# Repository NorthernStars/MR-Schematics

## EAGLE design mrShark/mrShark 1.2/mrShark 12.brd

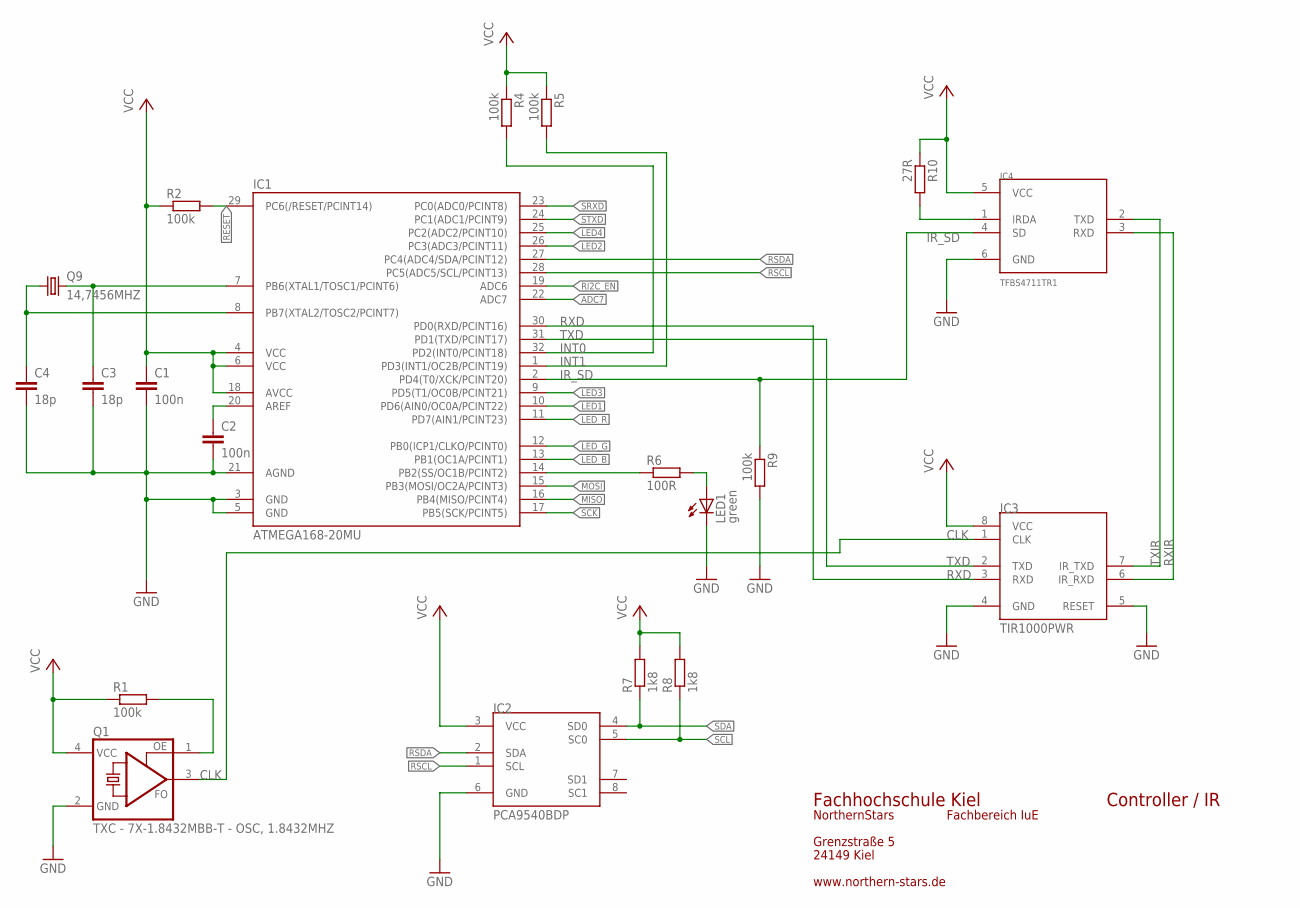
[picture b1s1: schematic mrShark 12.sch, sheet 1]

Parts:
C1, C2: 100n; C0201
C3, C4: 18p; C0201
IC1: ATMEGA168-20MU; MLF32
IC2: PCA9540BDP; TSSOP8
IC3: TIR1000PWR; PW_R-PDSO-G08
IC4: TFBS4711TR1; TFBS4711
LED1: green; CHIPLED_0603
Q1: TXC - 7X-1.8432MBB-T - OSC, 1.8432MHZ; 3.2X2.5
Q9: 14,7456MHZ; TXC_7B_SERIES
R1, R2, R4, R5, R9: 100k; R0201
R6: 100R; R0201
R7, R8: 1k8; R0201
R10: 27R; R0201

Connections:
ADC7: IC1.22 (ADC7); also elsewhere on the board
CLK: IC3.1 (CLK), Q1.3 (FO)
GND: C1.2, C2.2, C3.2, C4.2, IC1.3 (GND), IC1.5 (GND), IC1.21 (AGND), IC2.6 (GND), IC3.4 (GND), IC3.5 (RESET), IC4.6 (GND), LED1.C, Q1.2 (GND), R9.2; also elsewhere on the board
INT0: IC1.32 (PD2(INT0/PCINT18)), R4.2; also elsewhere on the board
INT1: IC1.1 (PD3(INT1/OC2B/PCINT19)), R5.2; also elsewhere on the board
IRDA: IC4.1 (IRDA), R10.2
IR_SD: IC1.2 (PD4(T0/XCK/PCINT20)), IC4.4 (SD), R9.1
LED1: IC1.10 (PD6(AIN0/OC0A/PCINT22)); also elsewhere on the board
LED2: IC1.26 (PC3(ADC3/PCINT11)); also elsewhere on the board
LED3: IC1.9 (PD5(T1/OC0B/PCINT21)); also elsewhere on the board
LED4: IC1.25 (PC2(ADC2/PCINT10)); also elsewhere on the board
LED_B: IC1.13 (PB1(OC1A/PCINT1)); also elsewhere on the board
LED_G: IC1.12 (PB0(ICP1/CLKO/PCINT0)); also elsewhere on the board
LED_R: IC1.11 (PD7(AIN1/PCINT23)); also elsewhere on the board
MISO: IC1.16 (PB4(MISO/PCINT4)); also elsewhere on the board
MOSI: IC1.15 (PB3(MOSI/OC2A/PCINT3)); also elsewhere on the board
unnamed: IC1.14 (PB2(SS/OC1B/PCINT2)), R6.1
unnamed: Q1.1 (OE), R1.2
unnamed: LED1.A, R6.2
unnamed: C2.1, IC1.20 (AREF)
RESET: IC1.29 (PC6(/RESET/PCINT14)), R2.2; also elsewhere on the board
RI2C_EN: IC1.19 (ADC6)
RSCL: IC1.28 (PC5(ADC5/SCL/PCINT13)), IC2.1 (SCL); also elsewhere on the board
RSDA: IC1.27 (PC4(ADC4/SDA/PCINT12)), IC2.2 (SDA); also elsewhere on the board
RXD: IC1.30 (PD0(RXD/PCINT16)), IC3.3 (RXD)
RXIR: IC3.6 (IR_RXD), IC4.3 (RXD)
SCK: IC1.17 (PB5(SCK/PCINT5)); also elsewhere on the board
SCL: IC2.5 (SC0), R8.1; also elsewhere on the board
SDA: IC2.4 (SD0), R7.1; also elsewhere on the board
SRXD: IC1.23 (PC0(ADC0/PCINT8)); also elsewhere on the board
STXD: IC1.24 (PC1(ADC1/PCINT9)); also elsewhere on the board
TXD: IC1.31 (PD1(TXD/PCINT17)), IC3.2 (TXD)
TXIR: IC3.7 (IR_TXD), IC4.2 (TXD)
VCC: C1.1, IC1.4 (VCC), IC1.6 (VCC), IC1.18 (AVCC), IC2.3 (VCC), IC3.8 (VCC), IC4.5 (VCC), Q1.4 (VCC), R1.1, R2.1, R4.1, R5.1, R7.2, R8.2, R10.1; also elsewhere on the board
XTAL1: C3.1, IC1.7 (PB6(XTAL1/TOSC1/PCINT6)), Q9.3 (2)
XTAL2: C4.1, IC1.8 (PB7(XTAL2/TOSC2/PCINT7)), Q9.1

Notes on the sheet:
Fachhochschule Kiel
Grenzstraße 5
24149 Kiel
NorthernStars
Fachbereich IuE
www.northern-stars.de
Controller / IR

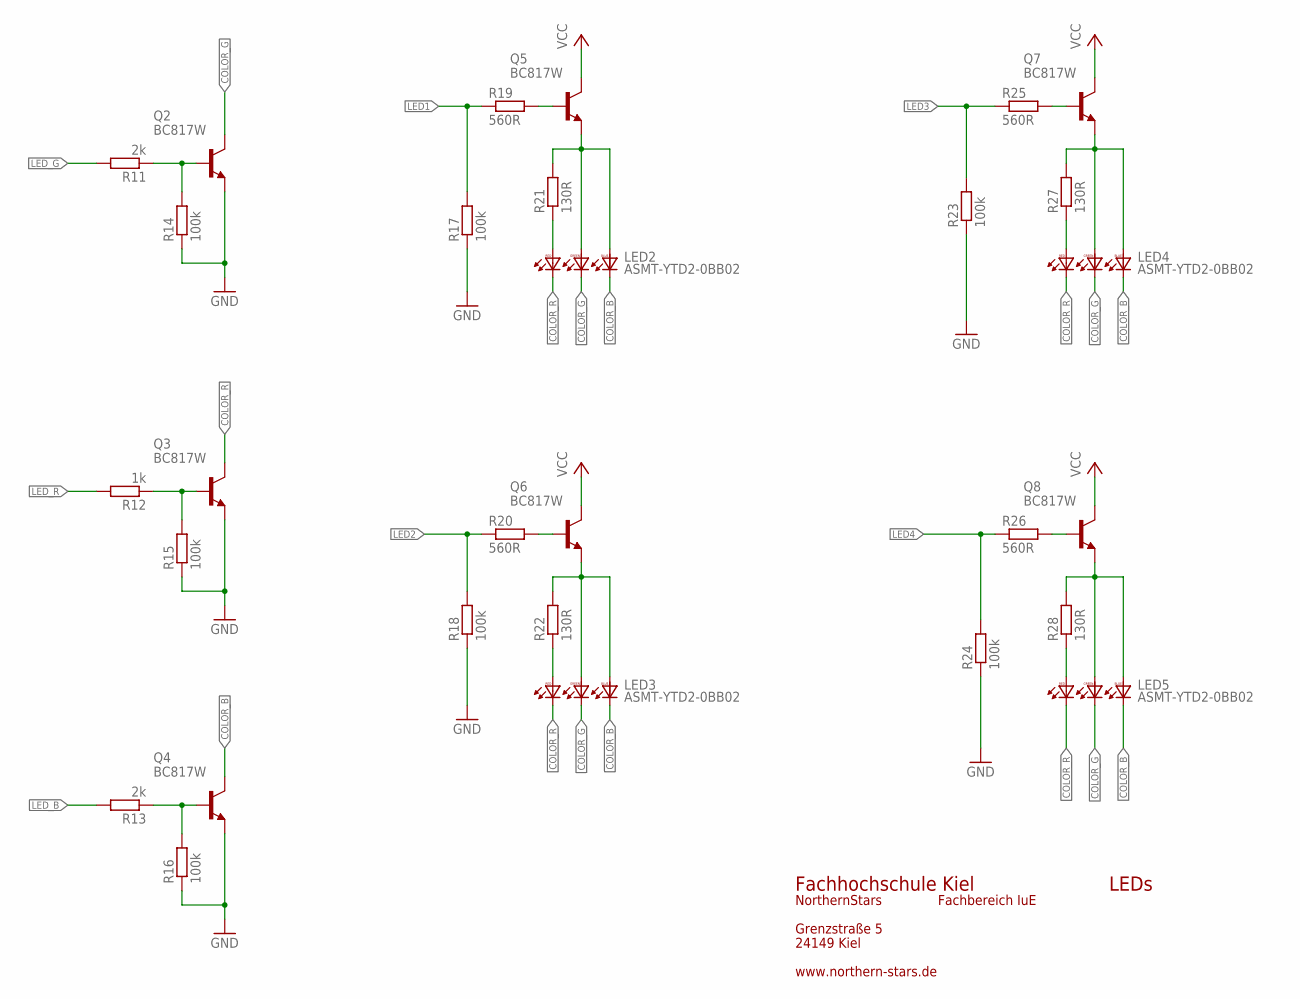
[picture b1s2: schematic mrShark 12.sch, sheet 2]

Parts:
LED2, LED3, LED4, LED5: ASMT-YTD2-0BB02; PLCC6K
Q2, Q3, Q4, Q5, Q6, Q7, Q8: BC817W; SOT323-BEC
R11, R13: 2k; R0201
R12: 1k; R0201
R14, R15, R16, R17, R18, R23, R24: 100k; R0201
R19, R20, R25, R26: 560R; R0201
R21, R22, R27, R28: 130R; R0201

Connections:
COLOR_B: LED2.1 (BC), LED3.1 (BC), LED4.1 (BC), LED5.1 (BC), Q4.C
COLOR_G: LED2.2 (GC), LED3.2 (GC), LED4.2 (GC), LED5.2 (GC), Q2.C
COLOR_R: LED2.3 (RC), LED3.3 (RC), LED4.3 (RC), LED5.3 (RC), Q3.C
GND: Q2.E, Q3.E, Q4.E, R14.1, R15.1, R16.1, R17.1, R18.1, R23.1, R24.1; also elsewhere on the board
LED1: R17.2, R19.1; also elsewhere on the board
LED2: R18.2, R20.1; also elsewhere on the board
LED3: R23.2, R25.1; also elsewhere on the board
LED4: R24.2, R26.1; also elsewhere on the board
LED_B: R13.2; also elsewhere on the board
LED_G: R11.2; also elsewhere on the board
LED_R: R12.2; also elsewhere on the board
unnamed: LED2.4 (RA), R21.1
unnamed: LED4.4 (RA), R27.1
unnamed: LED4.5 (GA), LED4.6 (BA), Q7.E, R27.2
unnamed: LED3.4 (RA), R22.1
unnamed: LED3.5 (GA), LED3.6 (BA), Q6.E, R22.2
unnamed: Q6.B, R20.2
unnamed: LED5.4 (RA), R28.1
unnamed: LED5.5 (GA), LED5.6 (BA), Q8.E, R28.2
unnamed: Q8.B, R26.2
unnamed: Q7.B, R25.2
unnamed: Q5.B, R19.2
unnamed: LED2.5 (GA), LED2.6 (BA), Q5.E, R21.2
VCC: Q5.C, Q6.C, Q7.C, Q8.C; also elsewhere on the board
X1: Q4.B, R13.1, R16.2
X2: Q3.B, R12.1, R15.2
X3: Q2.B, R11.1, R14.2

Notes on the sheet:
LEDs
Fachhochschule Kiel
Grenzstraße 5
24149 Kiel
NorthernStars
Fachbereich IuE
www.northern-stars.de

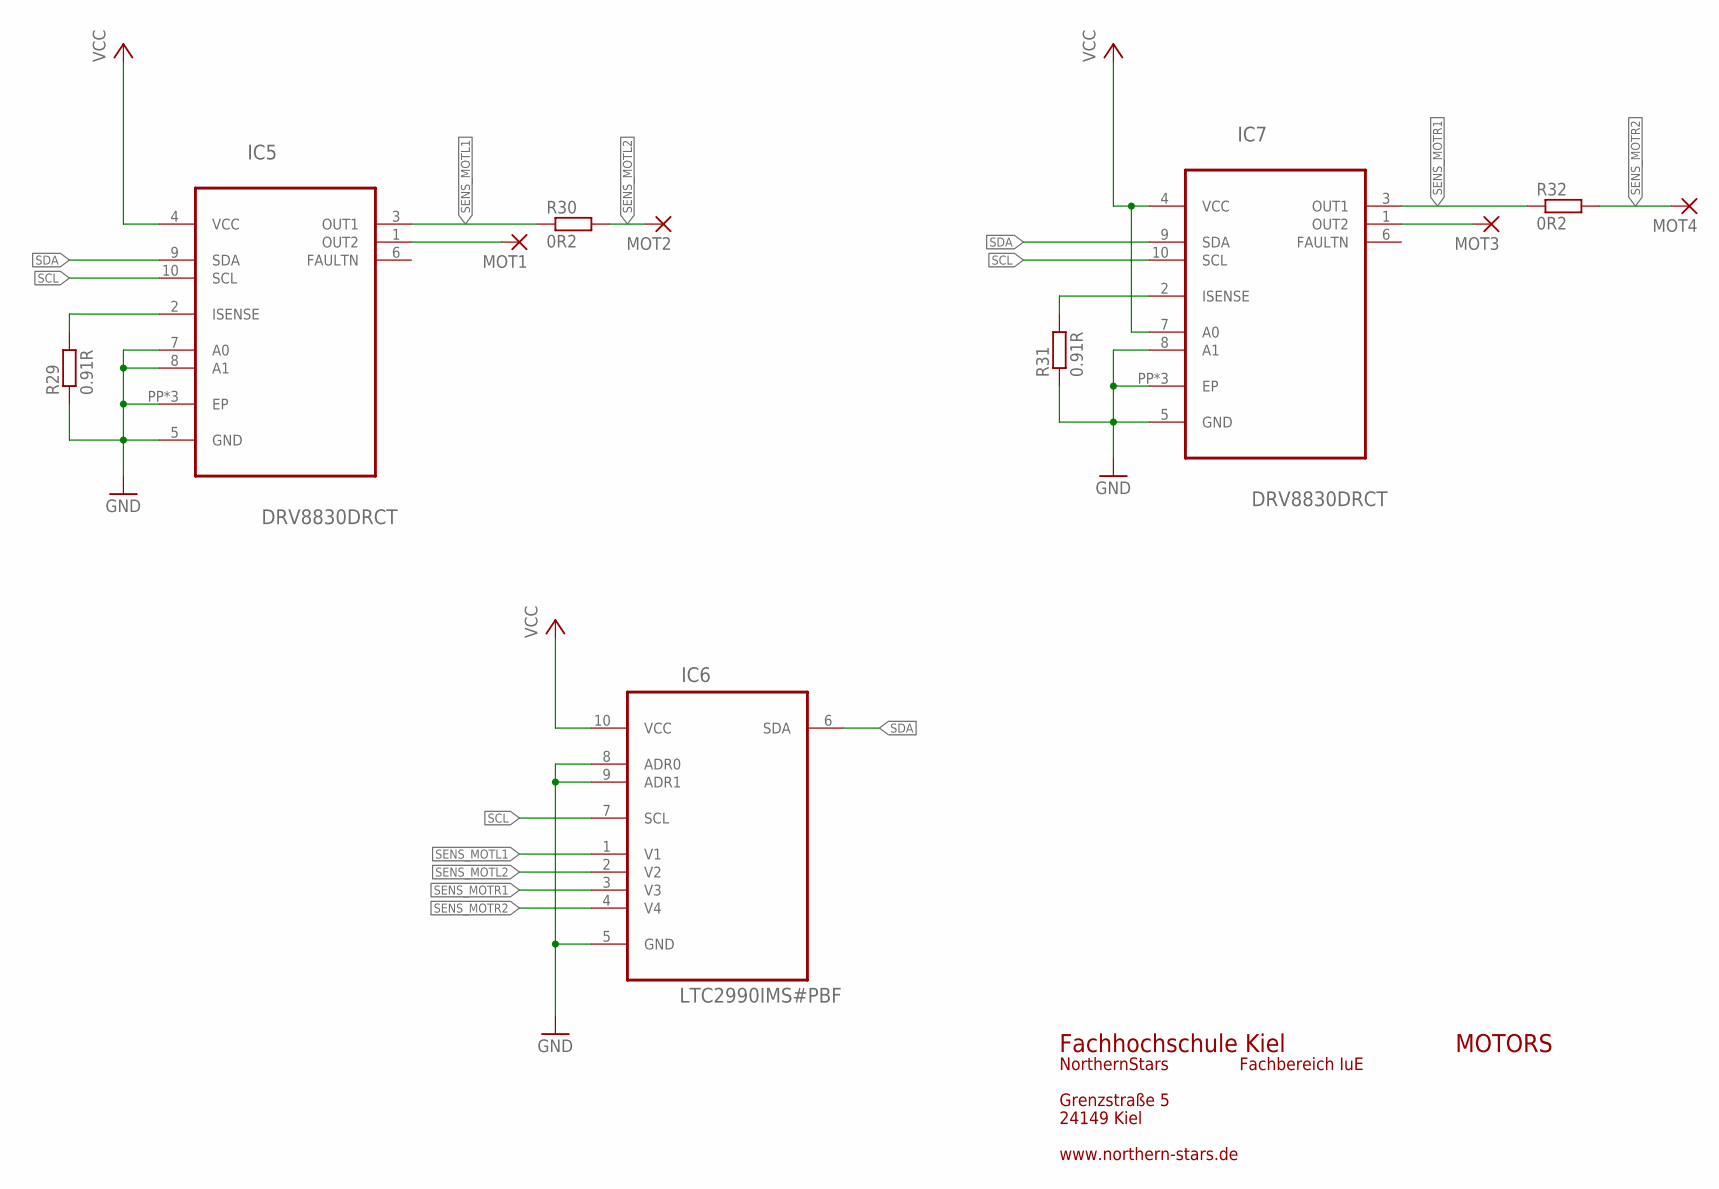
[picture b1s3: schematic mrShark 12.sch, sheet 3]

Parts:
IC5, IC7: DRV8830DRCT; S-PDSO-N10
IC6: LTC2990IMS#PBF; SOP50P490X110-10N
MOT1, MOT2, MOT3, MOT4: 1,6/0,9
R29, R31: 0.91R; R0603
R30, R32: 0R2; R0603

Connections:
GND: IC5.5 (GND), IC5.7 (A0), IC5.8 (A1), IC5.PP (EP), IC5.PP@1 (EP), IC5.PP@2 (EP), IC6.5 (GND), IC6.8 (ADR0), IC6.9 (ADR1), IC7.5 (GND), IC7.8 (A1), IC7.PP (EP), IC7.PP@1 (EP), IC7.PP@2 (EP), R29.1, R31.1; also elsewhere on the board
unnamed: IC5.1 (OUT2), MOT1.1
unnamed: IC5.2 (ISENSE), R29.2
unnamed: IC7.1 (OUT2), MOT3.1
unnamed: IC7.2 (ISENSE), R31.2
SCL: IC5.10 (SCL), IC6.7 (SCL), IC7.10 (SCL); also elsewhere on the board
SDA: IC5.9 (SDA), IC6.6 (SDA), IC7.9 (SDA); also elsewhere on the board
SENS_MOTL1: IC5.3 (OUT1), IC6.1 (V1), R30.1
SENS_MOTL2: IC6.2 (V2), MOT2.1, R30.2
SENS_MOTR1: IC6.3 (V3), IC7.3 (OUT1), R32.1
SENS_MOTR2: IC6.4 (V4), MOT4.1, R32.2
VCC: IC5.4 (VCC), IC6.10 (VCC), IC7.4 (VCC), IC7.7 (A0); also elsewhere on the board

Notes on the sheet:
MOTORS
Fachhochschule Kiel
Grenzstraße 5
24149 Kiel
NorthernStars
Fachbereich IuE
www.northern-stars.de

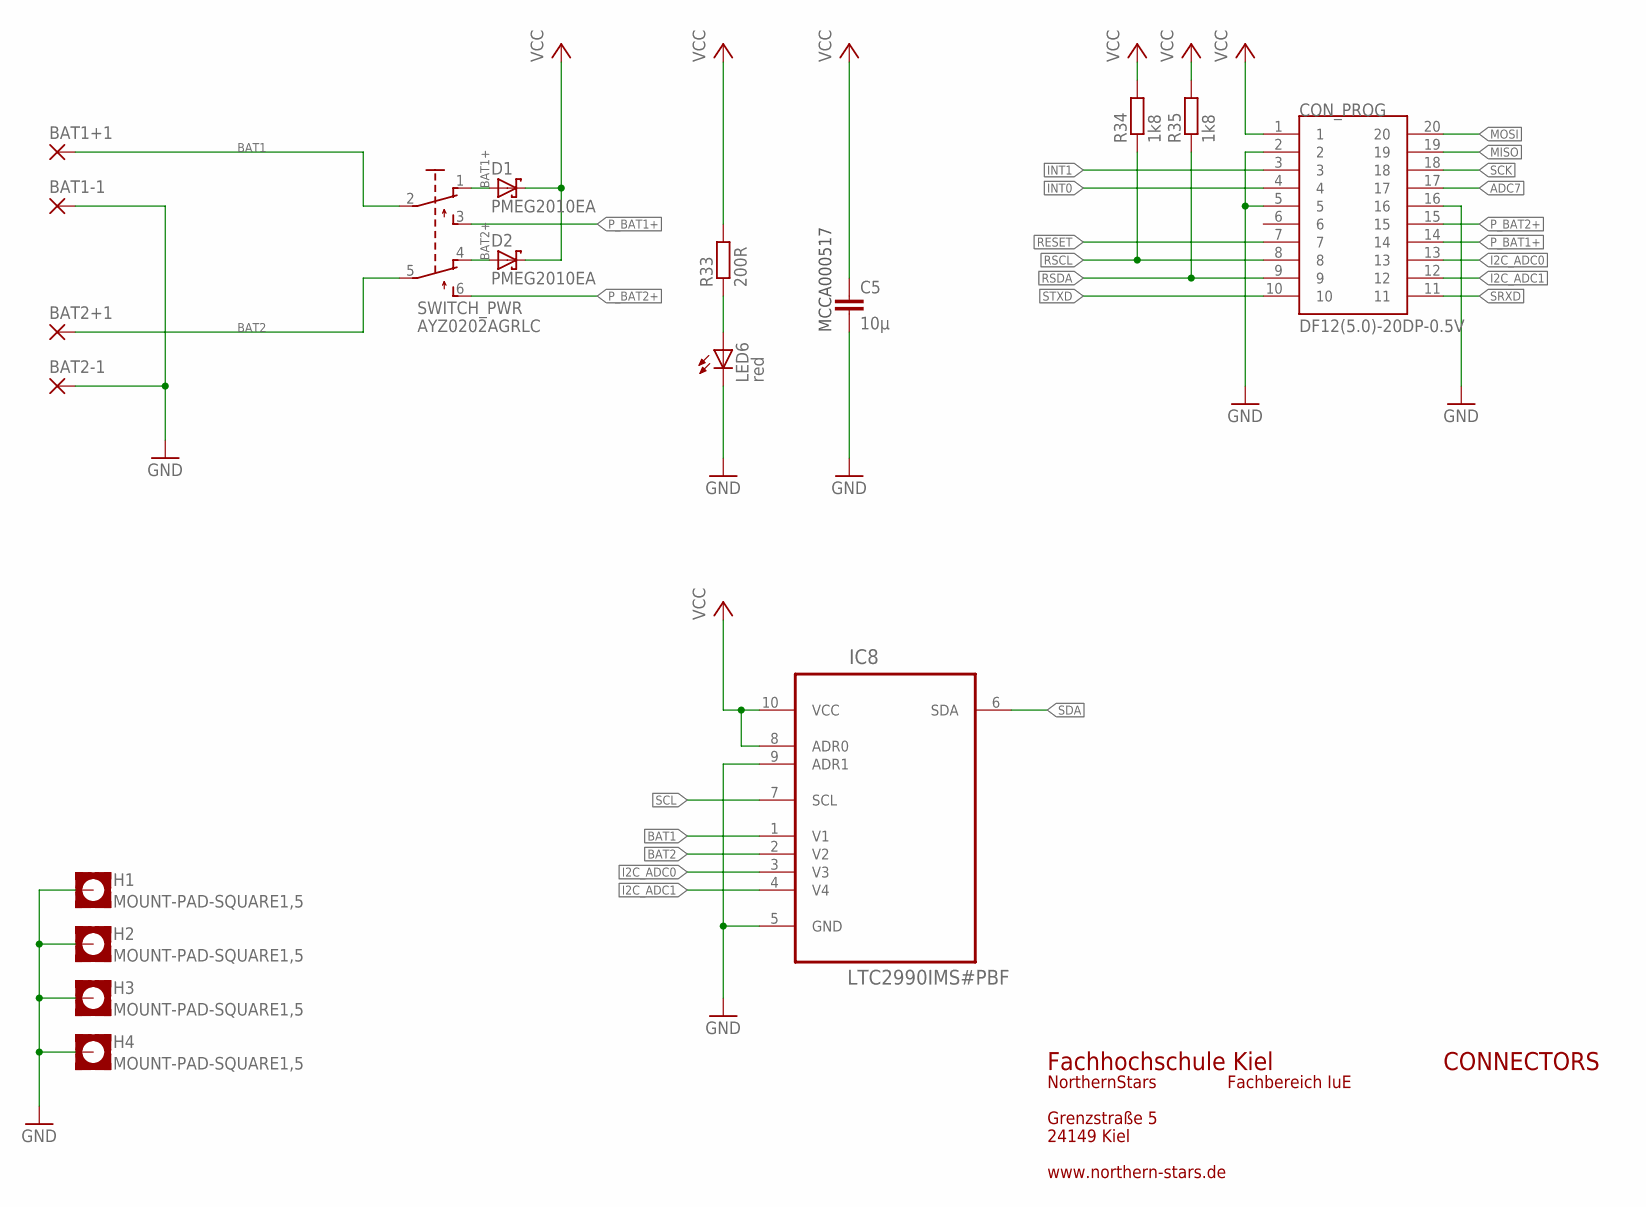
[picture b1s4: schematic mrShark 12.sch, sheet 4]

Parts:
BAT1+1, BAT1-1, BAT2+1, BAT2-1: 1,6/0,9
C5: 10µ; C0603K
CON_PROG: DF12(5.0)-20DP-0.5V; DF12-20DP
D1, D2: PMEG2010EA; SOD323-R
H1, H2, H3, H4: MOUNT-PAD-SQUARE1,5; 0,75-PAD-SQUARE
IC8: LTC2990IMS#PBF; SOP50P490X110-10N
LED6: red; CHIPLED_0603
R33: 200R; R0201
R34, R35: 1k8; R0201
SWITCH_PWR: AYZ0202AGRLC; AYZ0202AGLRC

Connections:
ADC7: CON_PROG.17; also elsewhere on the board
BAT1: BAT1+1.1, IC8.1 (V1), SWITCH_PWR.2
BAT1+: D1.A, SWITCH_PWR.1 (O)
BAT2: BAT2+1.1, IC8.2 (V2), SWITCH_PWR.5 (P1)
BAT2+: D2.A, SWITCH_PWR.4 (O1)
GND: BAT1-1.1, BAT2-1.1, C5.2, CON_PROG.2, CON_PROG.5, CON_PROG.16, H1.P, H2.P, H3.P, H4.P, IC8.5 (GND), IC8.9 (ADR1), LED6.C; also elsewhere on the board
I2C_ADC0: CON_PROG.13, IC8.3 (V3)
I2C_ADC1: CON_PROG.12, IC8.4 (V4)
INT0: CON_PROG.4; also elsewhere on the board
INT1: CON_PROG.3; also elsewhere on the board
MISO: CON_PROG.19; also elsewhere on the board
MOSI: CON_PROG.20; also elsewhere on the board
unnamed: LED6.A, R33.1
P_BAT1+: CON_PROG.14, SWITCH_PWR.3 (S)
P_BAT2+: CON_PROG.15, SWITCH_PWR.6 (S1)
RESET: CON_PROG.7; also elsewhere on the board
RSCL: CON_PROG.8, R34.1; also elsewhere on the board
RSDA: CON_PROG.9, R35.1; also elsewhere on the board
SCK: CON_PROG.18; also elsewhere on the board
SCL: IC8.7 (SCL); also elsewhere on the board
SDA: IC8.6 (SDA); also elsewhere on the board
SRXD: CON_PROG.11; also elsewhere on the board
STXD: CON_PROG.10; also elsewhere on the board
VCC: C5.1, CON_PROG.1, D1.C, D2.C, IC8.8 (ADR0), IC8.10 (VCC), R33.2, R34.2, R35.2; also elsewhere on the board

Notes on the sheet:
CONNECTORS
Fachhochschule Kiel
Grenzstraße 5
24149 Kiel
NorthernStars
Fachbereich IuE
www.northern-stars.de
MCCA000517

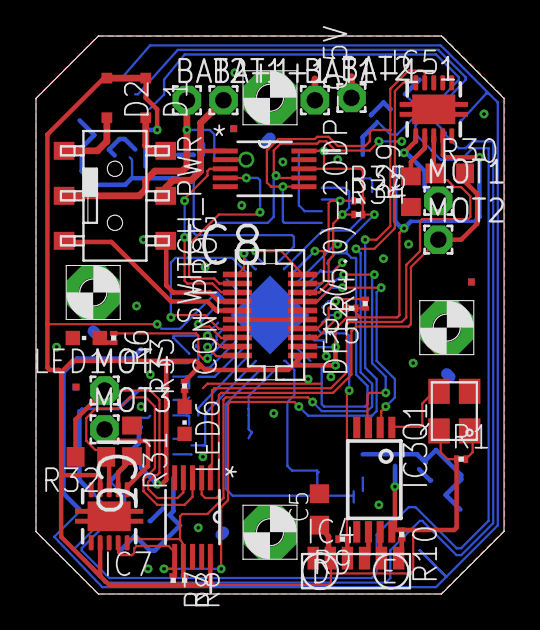
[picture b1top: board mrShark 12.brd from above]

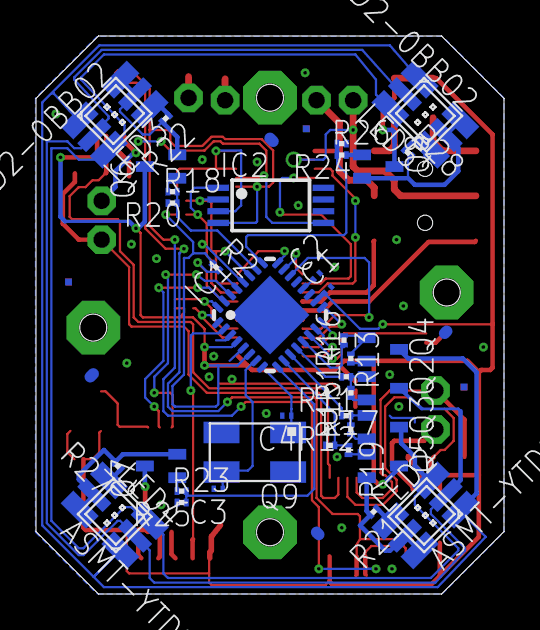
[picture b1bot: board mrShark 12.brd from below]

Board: 2 copper layers, 26.0 x 31.0 mm, 78 parts (37 on the bottom side), 70 nets.

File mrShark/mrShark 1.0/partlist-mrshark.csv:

sep=;
Quantity;Partname;Value;Package
2; C1, C2; 100n; C0201
2; C3, C4; 18p; C0201
1; CON_PROG; DF12(5.0)-20DP-0.5V; DF12-20DP
2; D1, D2; PMEG2010EA; SOD323-R
1; IC1; ATMEGA168V-10MU; MLF32
1; IC2; PCA9540B; TSSOP8
1; IC3; TIR1000PWR; PW_R-PDSO-G08
1; IC4; TFBS4711TR1; TFBS4711
2; IC5, IC7; DRV8830DRCT; S-PDSO-N10
2; IC6, IC8; LTC2990IMS#PBF; SOP50P490X110-10N
1; LED1; green; CHIPLED_0603
4; LED2, LED3, LED4, LED5; ASMT-YTD2-0BB02; PLCC6K
1; LED6; red; CHIPLED_0603
1; Q1; FXO-HC536R-1.8432 ; 3.2X2.5
7; Q2, Q3, Q4, Q5, Q6, Q7, Q8; BC817W; SOT323-BEC
1; Q9; 11.0592MHZ; TXC_7B_SERIES
12; R1, R2, R4, R5, R9, R14, R15, R16, R17, R18, R23, R24; 100k; R0201
6; R6, R21, R22, R27, R28, R33; 130R; R0201
4; R7, R8, R34, R35; 1k8; R0201
1; R10; 27R; R0201
2; R11, R13; 2k; R0201
1; R12; 1k; R0201
4; R19, R20, R25, R26; 560R; R0201
2; R29, R31; 0.95R; R0603
2; R30, R32; 0R2; R0603
1; SWITCH_PWR; AYZ0202AGRLC; AYZ0202AGLRC

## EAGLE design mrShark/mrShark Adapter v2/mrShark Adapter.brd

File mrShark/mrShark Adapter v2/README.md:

# mrShark Adapter v2
Additional version of the mrShark Adapter that can be soldered by humans.

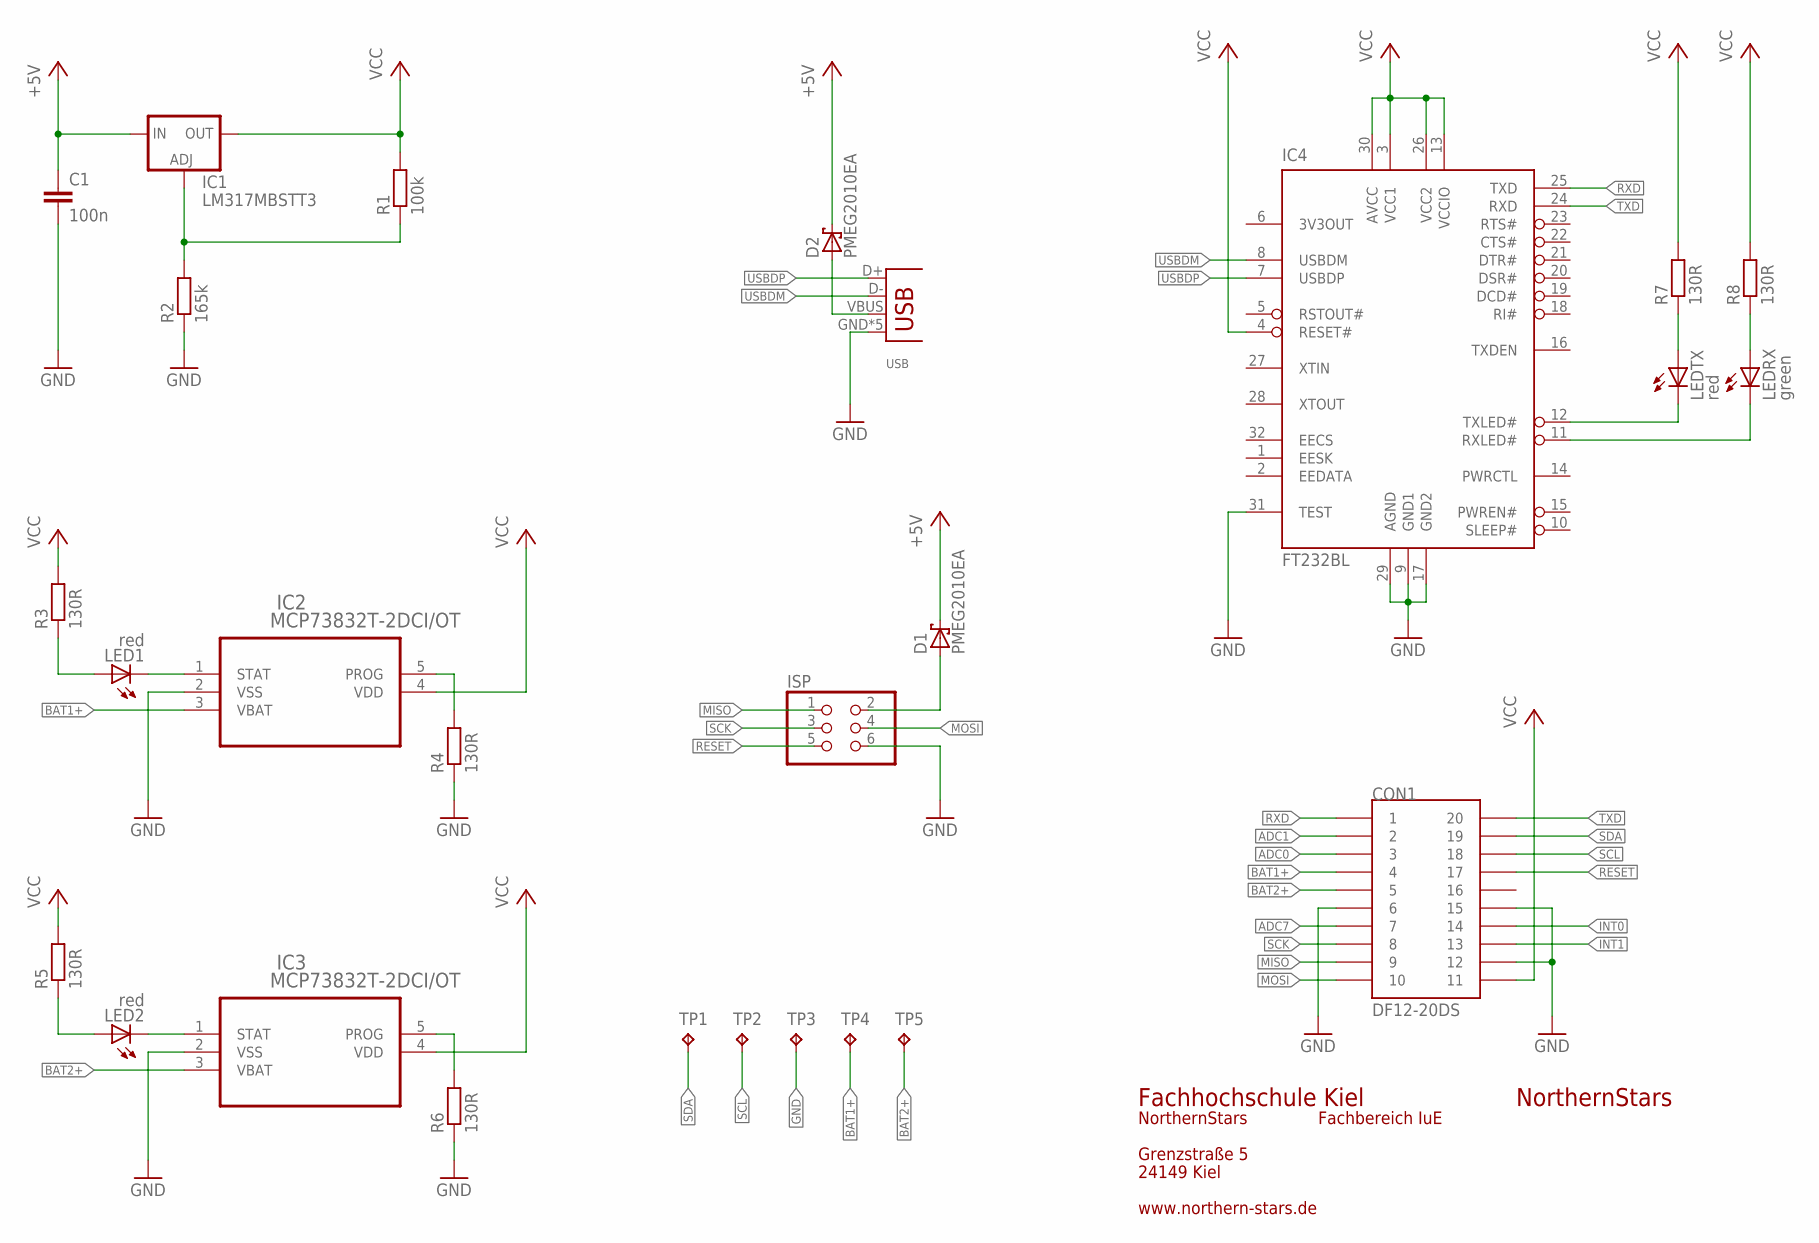
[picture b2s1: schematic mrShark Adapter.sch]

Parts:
C1: 100n; C0603
CON1: DF12-20DS
D1, D2: PMEG2010EA; SOD323-R
IC1: LM317MBSTT3; SOT223
IC2, IC3: MCP73832T-2DCI/OT; SOT95P300X145-5N
IC4: FT232BL; LQFP32
ISP: PINHD-2X03_2.54-SMD; 2X03SMD
LED1, LED2: red; CHIP-LED0603
LEDRX: green; CHIPLED_1206
LEDTX: red; CHIPLED_1206
R1: 100k; R0603
R2: 165k; R0603
R3, R4, R5, R6, R7, R8: 130R; R0603
TP1, TP2, TP3, TP4, TP5: TPTP06SQ; TP06SQ
USB: USB-MIC-S

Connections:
+5V: C1.1, D1.C, D2.C, IC1.3 (IN)
ADC0: CON1.3
ADC1: CON1.2
ADC7: CON1.7
BAT1+: CON1.4, IC2.3 (VBAT), TP4.TP
BAT2+: CON1.5, IC3.3 (VBAT), TP5.TP
GND: C1.2, CON1.6, CON1.12, CON1.15, IC2.2 (VSS), IC3.2 (VSS), IC4.9 (GND1), IC4.17 (GND2), IC4.29 (AGND), IC4.31 (TEST), ISP.6, R2.1, R4.1, R6.1, TP3.TP, USB.GND, USB.P$11 (GND), USB.P$12 (GND), USB.P$13 (GND), USB.P$14 (GND)
INT0: CON1.14
INT1: CON1.13
MISO: CON1.9, ISP.1
MOSI: CON1.10, ISP.4
unnamed: IC1.1 (ADJ), R1.1, R2.2
unnamed: IC2.1 (STAT), LED1.C
unnamed: LED1.A, R3.1
unnamed: D1.A, ISP.2
unnamed: IC2.5 (PROG), R4.2
unnamed: LED2.A, R5.1
unnamed: IC3.1 (STAT), LED2.C
unnamed: IC3.5 (PROG), R6.2
unnamed: D2.A, USB.VBUS
unnamed: IC4.12 (TXLED#), LEDTX.C
unnamed: IC4.11 (RXLED#), LEDRX.C
unnamed: LEDTX.A, R7.1
unnamed: LEDRX.A, R8.1
RESET: CON1.17, ISP.5
RXD: CON1.1, IC4.25 (TXD)
SCK: CON1.8, ISP.3
SCL: CON1.18, TP2.TP
SDA: CON1.19, TP1.TP
TXD: CON1.20, IC4.24 (RXD)
USBDM: IC4.8 (USBDM), USB.D-
USBDP: IC4.7 (USBDP), USB.D+
VCC: CON1.11, IC1.4 (OUT), IC2.4 (VDD), IC3.4 (VDD), IC4.3 (VCC1), IC4.4 (RESET#), IC4.13 (VCCIO), IC4.26 (VCC2), IC4.30 (AVCC), R1.2, R3.2, R5.2, R7.2, R8.2

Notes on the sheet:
NorthernStars
Fachhochschule Kiel
Grenzstraße 5
24149 Kiel
Fachbereich IuE
www.northern-stars.de

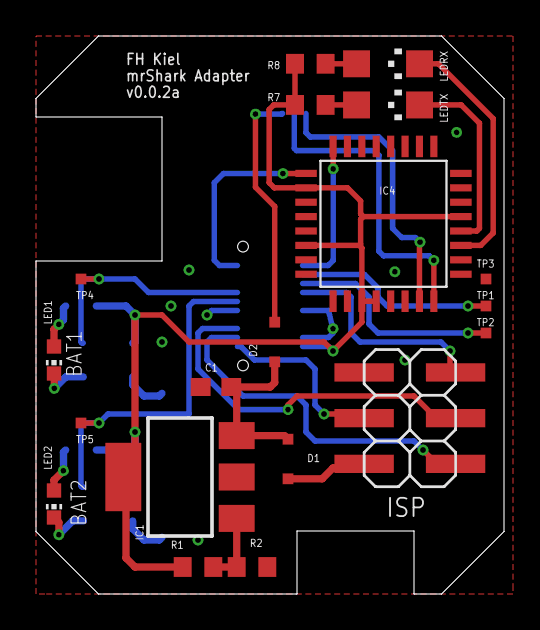
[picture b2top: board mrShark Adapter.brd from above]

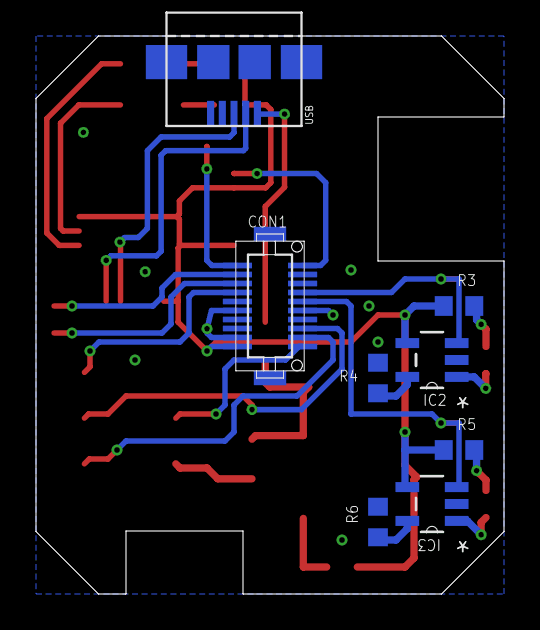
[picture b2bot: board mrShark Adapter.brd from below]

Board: 2 copper layers, 26.0 x 31.0 mm, 27 parts (8 on the bottom side), 28 nets.

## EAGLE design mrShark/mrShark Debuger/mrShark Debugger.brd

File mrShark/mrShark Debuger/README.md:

# mrShark Debugger
Debugging adapter using FT232 FTDI chip to translate controlers debugging uart to usb.

## DO NOT USE ANYMORE, LAYOUT OUTDATED

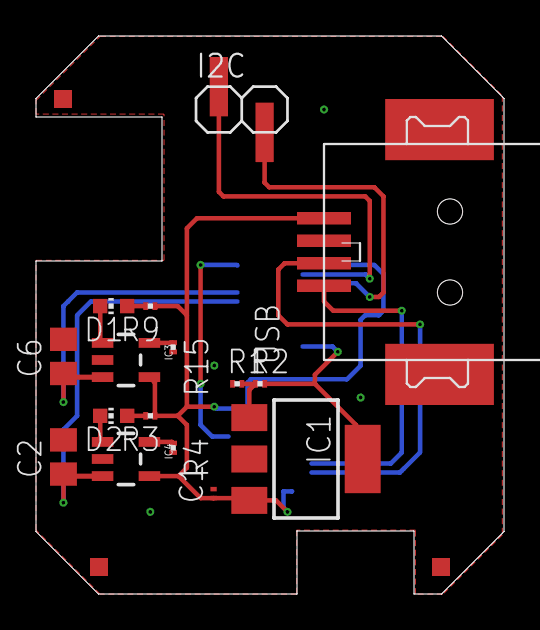
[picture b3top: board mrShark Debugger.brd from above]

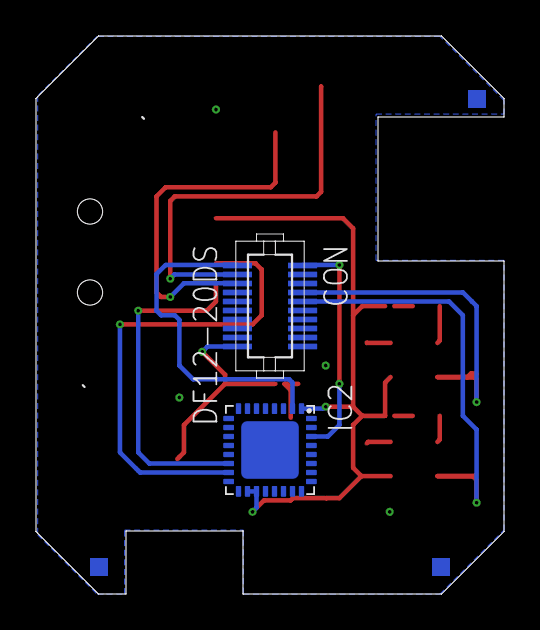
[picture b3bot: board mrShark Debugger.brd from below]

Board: 2 copper layers, 26.0 x 31.0 mm, 18 parts (2 on the bottom side), 18 nets.

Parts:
C1: 100n; C0201
C2, C6: 4.7uF; C0805
CON: DF12-20DS
D1, D2: RED; CHIP-LED0603
I2C: 1X02SMD
IC1: LM317MBSTT3; SOT223
IC2: FT232RQ; QFN32
IC3, IC4: MCP73831T-2ATI/OT; SOT23-5
R1: 165k; R0201
R2: 100k; R0201
R3, R9: 130R; R0201
R4, R15: 2K2; R0201
USB: USB-B-SMT

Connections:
+5V: C1.1, IC1.3, IC2.1, IC2.18, IC2.19, IC3.4, IC4.4, R3.1, R9.1, USB.VUSB
BAT1+: C6.1, CON.4, IC3.3
BAT2+: C2.1, CON.5, IC4.3
D+: IC2.14, USB.D+
D-: IC2.15, USB.D-
GND: C1.2, C2.2, C6.2, CON.6, CON.12, CON.15, CON.16, IC2.4, IC2.17, IC2.20, IC2.24, IC2.26, IC3.2, IC4.2, R1.1, R4.2, R15.2, USB.GND
unnamed: D1.A, R9.2
unnamed: D2.A, R3.2
unnamed: IC1.1, R1.2, R2.1
PROG: IC3.5, R15.1
PROG1: IC4.5, R4.1
RXD: CON.1, IC2.30
SCL: CON.18, I2C.2
SDA: CON.19, I2C.1
STAT: D1.C, IC3.1
STAT1: D2.C, IC4.1
TXD: CON.20, IC2.2
VCC: CON.11, IC1.4, R2.2
